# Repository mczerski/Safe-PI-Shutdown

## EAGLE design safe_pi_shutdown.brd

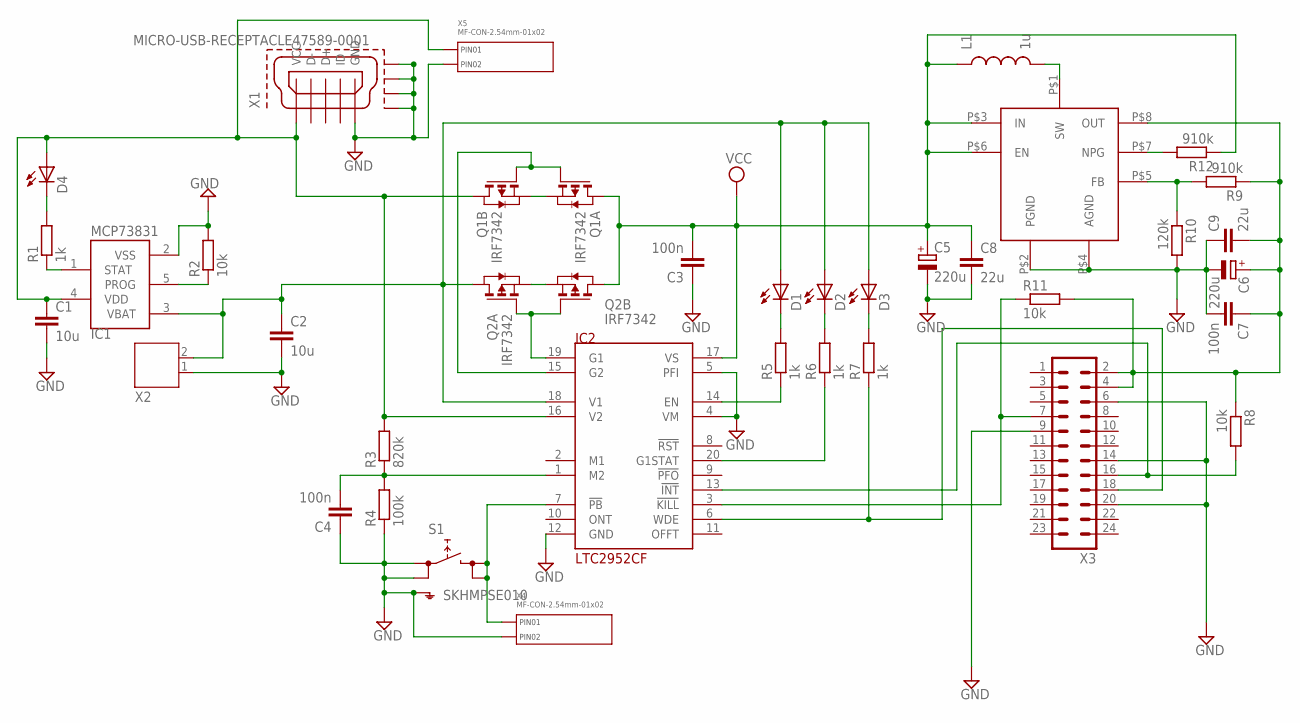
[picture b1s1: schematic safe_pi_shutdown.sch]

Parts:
C1, C2: 10u; C0603
C3, C4, C7: 100n; C0402
C5, C6: 220u; E3,5-8
C8, C9: 22u; C0603
D1, D2, D3, D4: LEDCHIPLED_0805; CHIPLED_0805
IC1: MCP73831; SOT23-5L
IC2: LTC2952CF; SSOP20
IC3: MIC2876
L1: 1u; CR54-KIT
Q1, Q2: IRF7342; SO8
R1, R5, R6, R7: 1k; R0603
R2, R8, R11: 10k; R0603
R3: 820k; R0603
R4: 100k; R0603
R9, R12: 910k; R0603
R10: 120k; R0603
S1: SKHMPSE010; SKHMPXE010
X1: MICRO-USB-RECEPTACLE47589-0001; 47589-0001
X2: JST-PH2
X3: MA12-2
X4, X5: MF-CON-2.54mm-01x02; PTH_2.54MM_01X02

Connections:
GND: C1.2, C2.2, C3.1, C4.1, C5.-, C6.-, C7.2, C8.2, C9.1, IC1.2 (VSS), IC2.4 (VM), IC2.5 (PFI), IC2.12 (GND), IC3.P$2 (PGND), IC3.P$4 (AGND), R2.2, R4.1, R10.2, S1.1 (1.1), S1.2 (1.2), S1.5 (SH), X1.5 (GND), X1.CASING1 (GND1), X1.CASING2 (GND2), X1.CASING3 (GND3), X1.CASING4 (GND4), X2.1, X3.6, X3.9, X3.14, X3.20, X4.P$2 (PIN2), X5.P$2 (PIN2)
unnamed: Q2.1 (S), Q2.3 (S)
unnamed: IC2.19 (G1), Q2.2 (G), Q2.4 (G)
unnamed: IC2.15 (G2), Q1.2 (G), Q1.4 (G)
unnamed: C6.+, C7.1, C9.2, IC3.P$8 (OUT), R8.1, R9.1, R11.2, X3.2, X3.4
unnamed: IC2.7 (!PB), S1.3 (2.1), S1.4 (2.2), X4.P$1 (PIN1)
unnamed: D4.C, R1.2
unnamed: IC3.P$5 (FB), R9.2, R10.1
unnamed: C4.2, IC2.1 (M2), R3.1, R4.2
unnamed: IC3.P$1 (SW), L1.P$2 (2)
unnamed: IC2.13 (!INT), R8.2, X3.16
unnamed: IC3.P$7 (NPG), R12.2
unnamed: IC2.3 (!KILL), R11.1, X3.7
unnamed: IC1.5 (PROG), R2.1
unnamed: D3.C, R7.2
unnamed: D1.C, R5.2
unnamed: IC2.14 (EN), R5.1
unnamed: IC2.6 (WDE), R7.1, X3.18
unnamed: IC2.20 (G1STAT), R6.1
unnamed: D2.C, R6.2
unnamed: IC1.1 (STAT), R1.1
unnamed: Q1.1 (S), Q1.3 (S)
V1: C2.1, D1.A, D2.A, D3.A, IC1.3 (VBAT), IC2.18 (V1), Q2.7 (D), Q2.8 (D), X2.2
V2: C1.1, D4.A, IC1.4 (VDD), IC2.16 (V2), Q1.5 (D), Q1.6 (D), R3.2, X1.1 (VCC), X5.P$1 (PIN1)
VCC: C3.2, C5.+, C8.1, IC2.17 (VS), IC3.P$3 (IN), IC3.P$6 (EN), L1.P$1 (1), Q1.7 (D), Q1.8 (D), Q2.5 (D), Q2.6 (D), R12.1

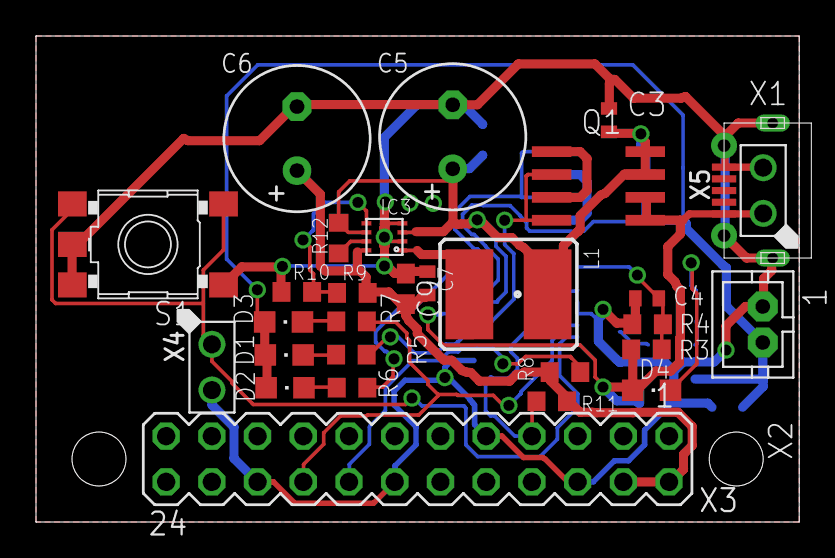
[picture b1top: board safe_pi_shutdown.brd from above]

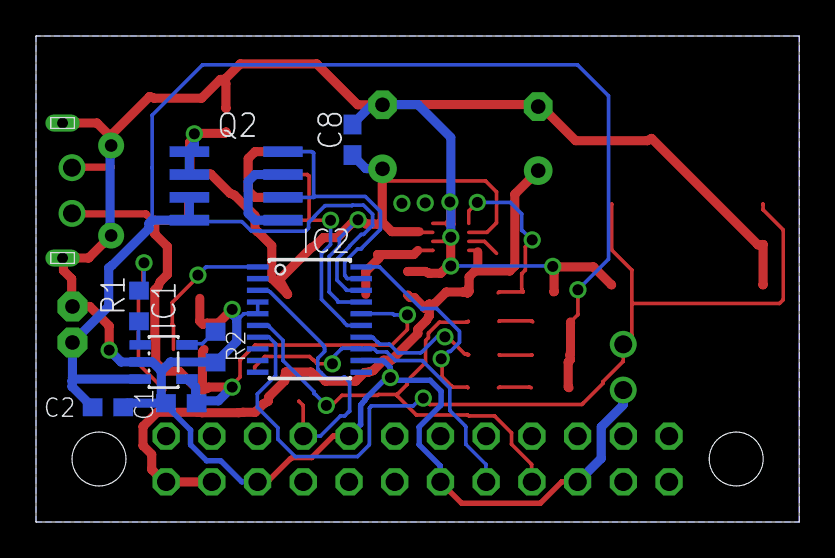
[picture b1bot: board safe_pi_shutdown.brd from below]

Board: 2 copper layers, 42.4 x 27.0 mm, 37 parts (8 on the bottom side), 25 nets.

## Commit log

2017-04-26 pierwszy commit
2017-04-26 prawie pierwsza wersja
2017-04-27 polaczone wszystkie sciezki
2017-04-28 rozmieszczenie nazw na layaoucie
2017-04-28 dostosowanie do nanopi zero (pozycja konektora)
2017-04-29 dodanie headerow do podlaczenia do plyty bazowej
2017-05-06 zmiana micro usb, poprawki z kondensatorami i inne
2017-05-06 przyciecie plytki do minimum
2017-05-06 poprawki
2017-05-21 nie wiem jakie zmiany
2017-06-15 dodanie pull-up dla pinu INT
2017-07-16 boost converter changed to MIC2876
2019-01-13 add more capacitors to power path
2019-01-16 convert eagle to kicad
2019-01-16 remove eagle project
2021-04-09 changes made automatically after opening project in newest kickad
    + added gitignore
2021-04-09 added TODO

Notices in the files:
parts and their libraries:
con-molex-usb: (C) 2014 Tomasz Boleslaw CEDRO, cederom@tlen.pl, http://www.tomek.cedro.info.
SparkFun-Passives: Licensing: Creative Commons ShareAlike 4.0 International - https://creativecommons.org/licenses/by-sa/4.0
